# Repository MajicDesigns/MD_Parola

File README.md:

# Library for modular scrolling LED matrix text displays

[Version 1.0 Video](http://www.youtube.com/watch?v=JgzVCSFaz3I)

[Version 2.0 Video](http://www.youtube.com/watch?v=u1iELyROjW8)

[Sprites Animation Video](http://www.youtube.com/watch?v=tfwAHx0MTxU)

[Library Documentation](https://majicdesigns.github.io/MD_Parola/)

Parola is a modular scrolling text display using MAX7219 or MAX7221 LED matrix display controllers using Arduino. The display is made up of any number of identical modules that are plugged together to create a wider/longer display.
* Text left, right or center justification in the display
* Text scrolling, entry and exit effects
* Control display parameters and animation speed
* Support for hardware SPI interface
* Multiple virtual displays (zones) in each string of LED modules
* User defined fonts and/or individual characters substitutions
* Support for double height displays
* Support for mixing text and graphics on the same display

The aim was to create a 'lego-like' LED matrix display, using standard 8x8 LED matrices. The software supports this flexibility through a scalable approach that only requires the definition of the number of modules to adapt existing software to a new configuration.

If you like and use this library please consider making a small donation using [PayPal](https://paypal.me/MajicDesigns/4USD)

The Parola software has a dependency on the [MD_MAX72xx Arduino library](https://github.com/MajicDesigns/MD_MAX72xx) which implements hardware functions of the LED matrix. The library needs to be configured for the type of matrices being used - please refer to the hardware section of documentation for the [MD_MAX72xx library](https://majicdesigns.github.io/MD_MAX72XX/page_hardware.html).

Parola discussion on the [Arduino forum](http://forum.arduino.cc/index.php?topic=171056.0) and kits available from [ElectroDragon](http://www.electrodragon.com/product/dot-matrix-chain-display-kit-max7219-v2).

Additional information also at [my blog](http://arduinoplusplus.wordpress.com), search "Parola A to Z".

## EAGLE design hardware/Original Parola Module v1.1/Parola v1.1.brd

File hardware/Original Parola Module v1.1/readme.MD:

Parola hardware documentation files for custom PCB
- Eagle CAD Schematic and Board layout
- SeeedStudio PCB manufacture Gerber files

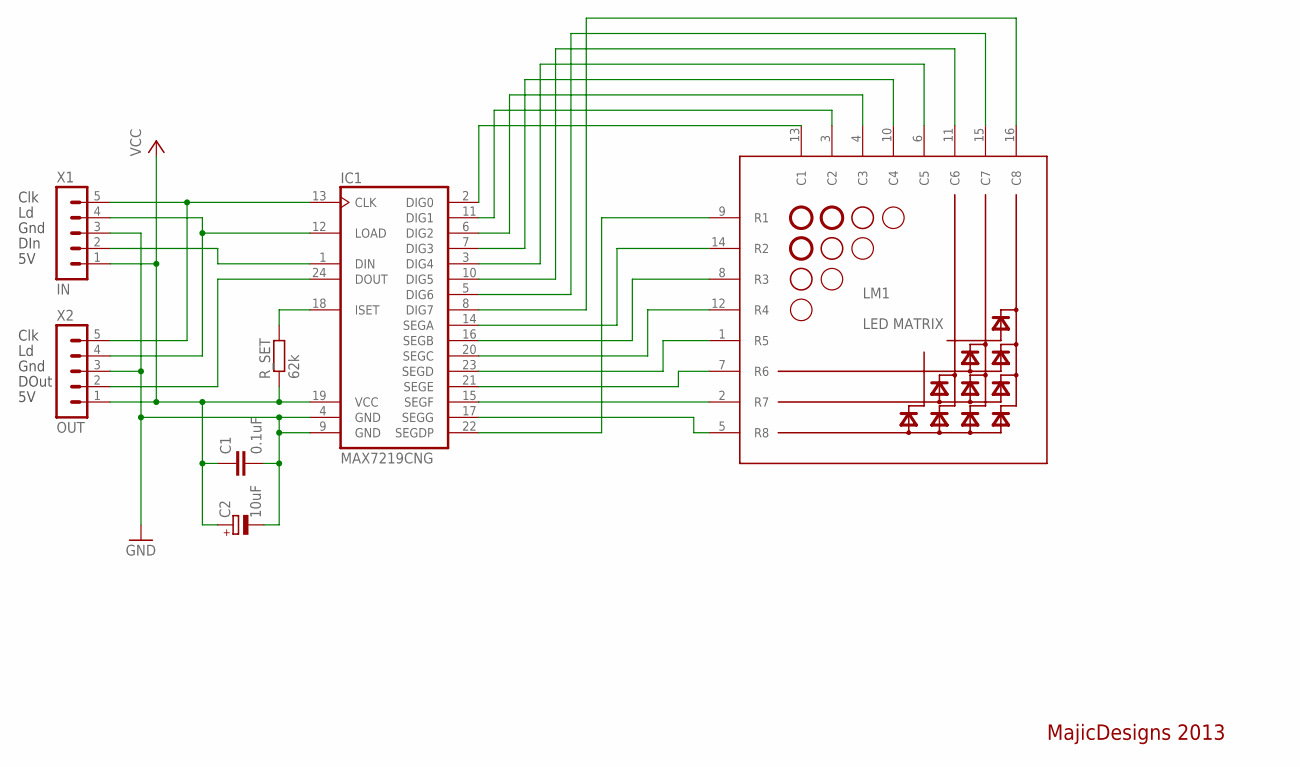
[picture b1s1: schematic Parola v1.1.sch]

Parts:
C1: 0.1uF; C025-024X044
C2: 10uF; E2-5
IC1: MAX7219CNG; DIL24-3
LM1: LED MATRIX; LED_MATRIX
R_SET: 62k; 0207/10
X1: IN; MAR05-1
X2: OUT; MAR05-1

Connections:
GND: C1.2, C2.-, IC1.4 (GND), IC1.9 (GND), X1.3, X2.3
unnamed: IC1.17 (SEGG), LM1.5 (R8)
unnamed: IC1.15 (SEGF), LM1.2 (R7)
unnamed: IC1.21 (SEGE), LM1.7 (R6)
unnamed: IC1.23 (SEGD), LM1.1 (R5)
unnamed: IC1.20 (SEGC), LM1.12 (R4)
unnamed: IC1.16 (SEGB), LM1.8 (R3)
unnamed: IC1.14 (SEGA), LM1.14 (R2)
unnamed: IC1.22 (SEGDP), LM1.9 (R1)
unnamed: IC1.8 (DIG7), LM1.16 (C8)
unnamed: IC1.5 (DIG6), LM1.15 (C7)
unnamed: IC1.10 (DIG5), LM1.11 (C6)
unnamed: IC1.3 (DIG4), LM1.6 (C5)
unnamed: IC1.7 (DIG3), LM1.10 (C4)
unnamed: IC1.6 (DIG2), LM1.4 (C3)
unnamed: IC1.11 (DIG1), LM1.3 (C2)
unnamed: IC1.2 (DIG0), LM1.13 (C1)
unnamed: IC1.13 (CLK), X1.5, X2.5
unnamed: IC1.12 (LOAD), X1.4, X2.4
unnamed: IC1.1 (DIN), X1.2
unnamed: IC1.24 (DOUT), X2.2
unnamed: IC1.18 (ISET), R_SET.2
VCC: C1.1, C2.+, IC1.19 (VCC), R_SET.1, X1.1, X2.1

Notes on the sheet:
Clk
Gnd
DIn
DOut
MajicDesigns 2013

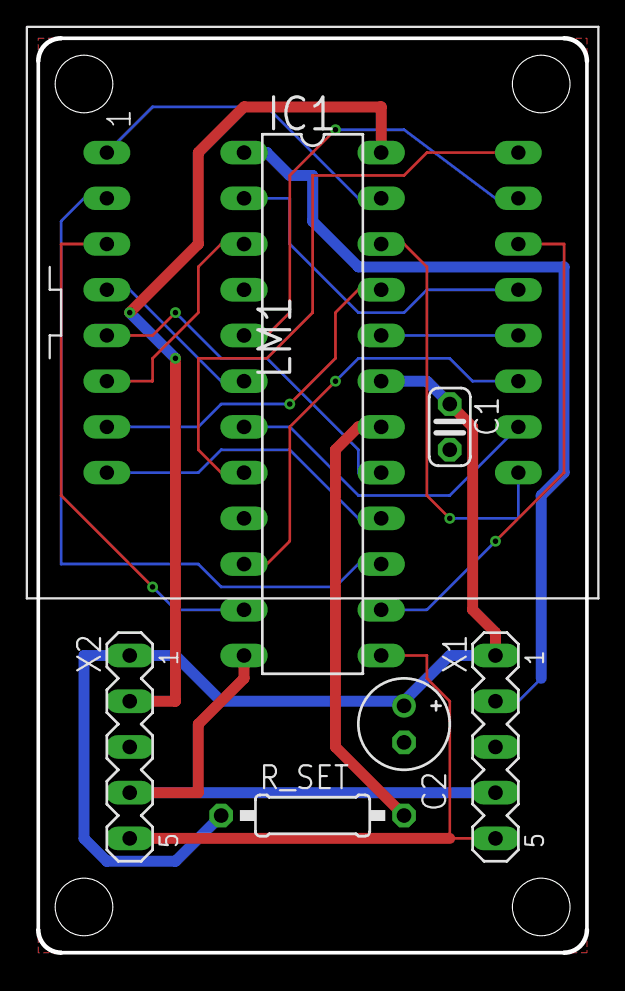
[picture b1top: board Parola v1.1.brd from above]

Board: 2 copper layers, 30.5 x 50.8 mm, 7 parts (0 on the bottom side), 23 nets.

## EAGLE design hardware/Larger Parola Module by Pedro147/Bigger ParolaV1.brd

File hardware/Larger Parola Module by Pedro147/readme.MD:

Bigger Parola V1

For anyone wanting to use slightly larger 60 mm LED matrices, here are the Eagle board and schematic files, seeedstudio gerbers and custom 8 x 8 LED matrix files. Link to Bigger Parola webpage where there are some images of the PCB's and an enclosure containing eight of these display matrices and operating controls. http://www.pedroduino.com/BiggerParolaforArduino.php

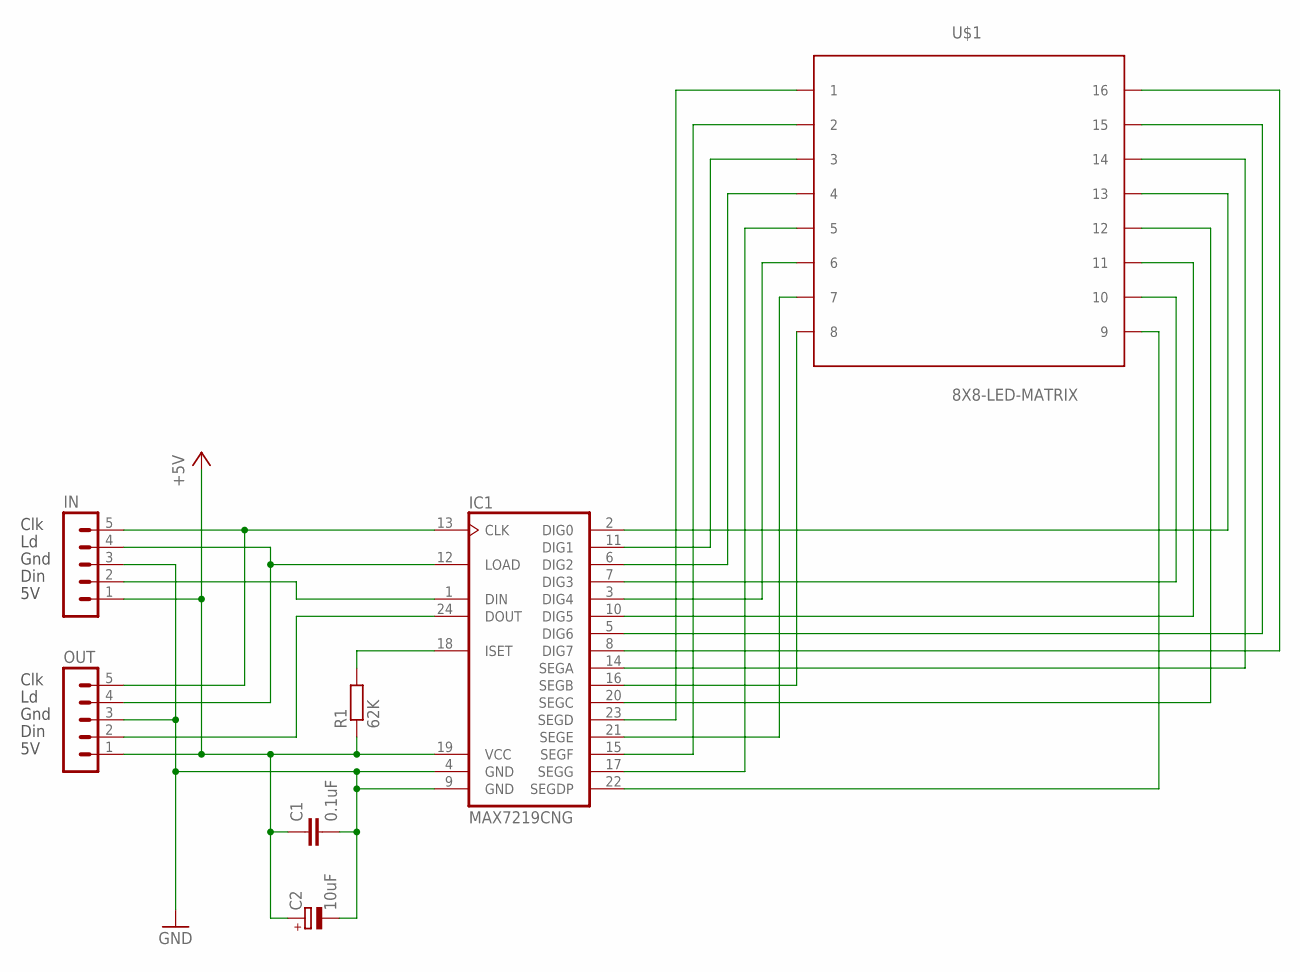
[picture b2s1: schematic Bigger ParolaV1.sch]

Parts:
C1: 0.1uF; C025-024X044
C2: 10uF; E2-5
IC1: MAX7219CNG; DIL24-3
IN: MAR05-1
OUT: MAR05-1
R1: 62K; 0207/10
U$1: 8X8-LED-MATRIX

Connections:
+5V: C1.1, C2.+, IC1.19 (VCC), IN.1, OUT.1, R1.1
GND: C1.2, C2.-, IC1.4 (GND), IC1.9 (GND), IN.3, OUT.3
unnamed: IC1.18 (ISET), R1.2
unnamed: IC1.24 (DOUT), OUT.2
unnamed: IC1.12 (LOAD), IN.4, OUT.4
unnamed: IC1.13 (CLK), IN.5, OUT.5
unnamed: IC1.1 (DIN), IN.2
unnamed: IC1.2 (DIG0), U$1.P$13 (13)
unnamed: IC1.11 (DIG1), U$1.P$3 (3)
unnamed: IC1.6 (DIG2), U$1.P$4 (4)
unnamed: IC1.7 (DIG3), U$1.P$10 (10)
unnamed: IC1.3 (DIG4), U$1.P$6 (6)
unnamed: IC1.10 (DIG5), U$1.P$11 (11)
unnamed: IC1.5 (DIG6), U$1.P$15 (15)
unnamed: IC1.8 (DIG7), U$1.P$16 (16)
unnamed: IC1.14 (SEGA), U$1.P$14 (14)
unnamed: IC1.16 (SEGB), U$1.P$8 (8)
unnamed: IC1.20 (SEGC), U$1.P$12 (12)
unnamed: IC1.23 (SEGD), U$1.P$1 (1)
unnamed: IC1.21 (SEGE), U$1.P$7 (7)
unnamed: IC1.15 (SEGF), U$1.P$2 (2)
unnamed: IC1.17 (SEGG), U$1.P$5 (5)
unnamed: IC1.22 (SEGDP), U$1.P$9 (9)

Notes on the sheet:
Clk
Gnd
Din

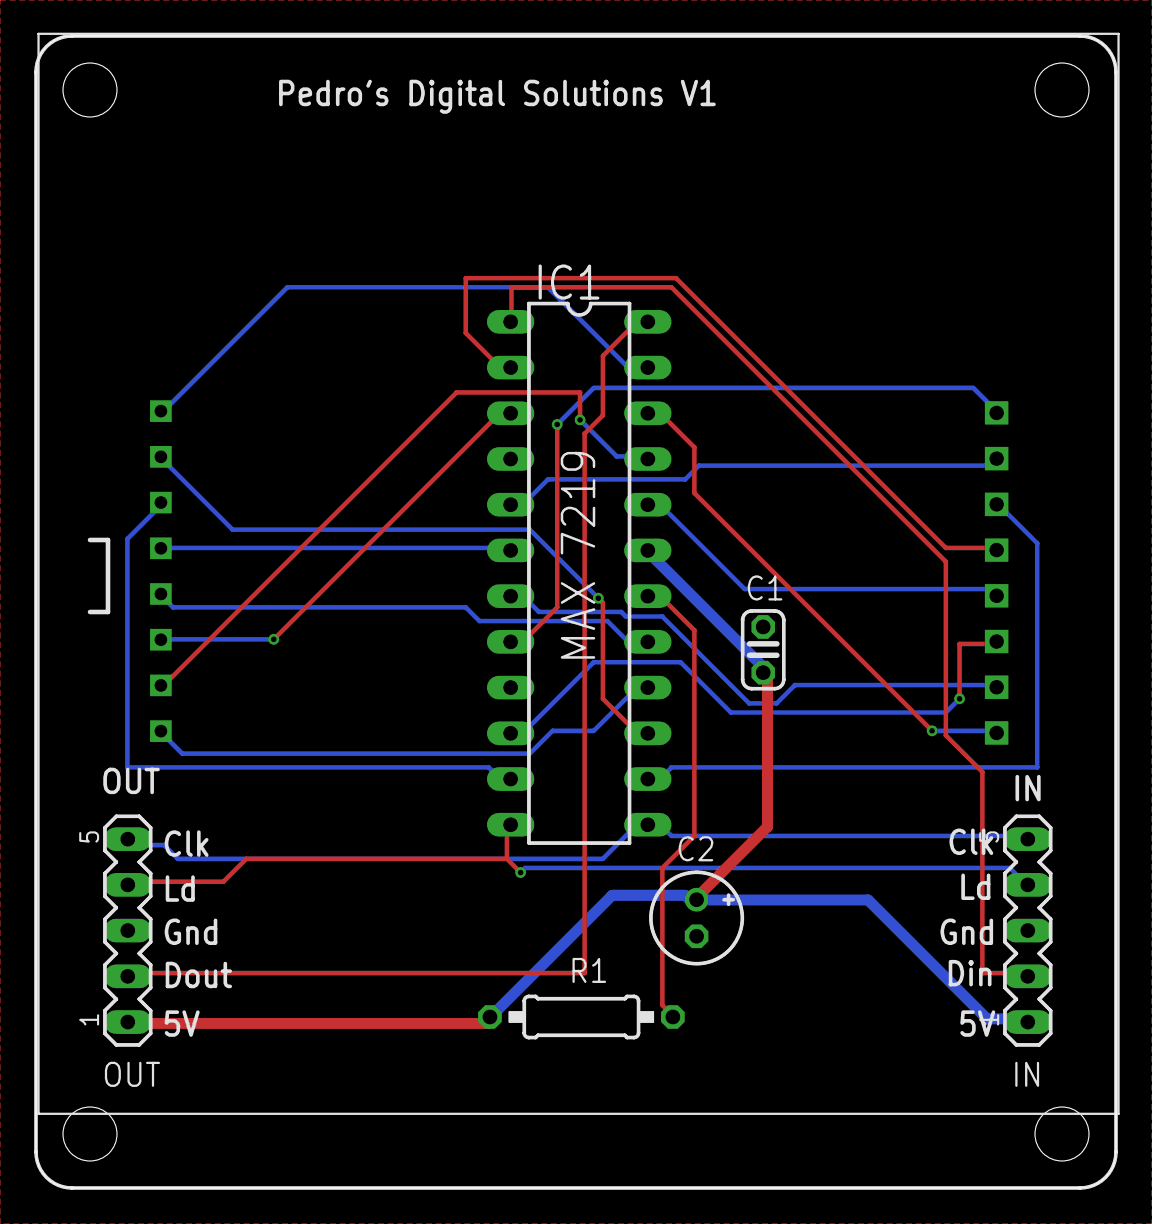
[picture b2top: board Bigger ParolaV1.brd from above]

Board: 2 copper layers, 60.0 x 64.0 mm, 7 parts (0 on the bottom side), 23 nets.

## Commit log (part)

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2013-11-23 First commit on version 1.0
2013-11-24 Changed web addresses to new location; spelling check of header file
2013-12-31 Minor changes
2014-02-15 Reworkd to allow user defined font files.
2014-02-15 Added functionality for usert defined character substitution
2014-02-16 Added animations SCAN_HORIZ, SCAN_VERT, GROW_UP, GROW_DOWN
2014-02-16 Removed static variables from effects functions in preparation for zoning code
2014-02-22 Reworked Parola test example program Fixed number of issues with the display of inverted messages on some effects.
2014-02-22 Adjusted fonts example for Arabic "Arduino" and modern font Test program changed after completion of test shield arrangement
2014-02-25 Added diagonal scrolling animations effects Modified examples to suit Changted H and V scrolling function parameters to be in line with rest
2014-03-09 Snapshot after major changes to MD_MAX library. Appears to still work ok :-) First checkin of images.
2014-03-11 First pass at zoning. Zones implemented in Parola object ready for creation of zone object as stage 2
2014-03-22 Fixed Slice animation with single default zone implementation Useing MD_KeySwitch object in example software
2014-03-22 End of day work for new zones. Still issues with Fonts and definitions but overall working reasonably
2014-03-24 Multi zone implementation completed. Fixed bug with Slice animation Added Zone examples.
2014-03-26 Completed implementation of zoned displays and tested. New examples included.
2014-03-28 Clean up ready for v2.0 release
2014-04-27 Minor corrections to comments and code
2014-07-25 Fixed animation timer bug and changed time profiling debug code
2014-09-06 Fixed animation issues with SCAN_VERT and SLICE. Added Animations Catalog example program. Renamed Doxyfile config file.
2014-09-14 Fixed compile errors woith PROGMEM and IDE v1.5.7
2015-01-31 Version 2.1 Release - includes all changes since version 2.0
2015-02-13 Added Scrolling_ML example
2015-03-03 Added Zone_Mesg example
2015-03-06 Added overloaded displayClear() for zone
2015-03-07 Fixed bug in SLICE effect when text was too long for display
2015-03-31 src folder added for Library Manager (IDE 1.6.2)
2015-03-31 Version 2.2 code base
2015-06-15 Changes to accomodate adjustments to the MD_KeySwitch library
2015-07-19 - Added set/getScrollSpacing() methods - Added associated Scrolling_Spacing example New method allows for scrolled text to be on the display before the previous text has left the display.
2015-07-19 - Added set/getZoneEffect with FLIP_LR and FLIP_UD - Added associated Zone_Mirror example - Fixed minor bugs and documentation
2015-07-20 Minor tidy up from last commit - keywords.txt missing get/setZoneEffect() - Added flip test ui switch to Parola_Test - Changed timing in test catalog after fixing variable reference bug.
2015-08-17 Added MESH animation Souce code set for version 2.3 release
2015-09-05 Minor changes due to MD_DS1307 library change
2015-09-19 Added example to demonstrate dynamic zones
2015-09-24 Added synchZoneStart() method for zonbe animation
2015-09-27 Added double height example code by Arek00 Modifed all examples to conditionally include <SPI.h>
2015-10-03 Added additional example file that uses double height foints created with MD_MAX72xx font builder.
2015-10-20 Added HelloWorld example
2016-01-02 Added FADE effect. Reviewed and reorganised some documentation.
2016-01-02 Added #defines ENA_* for granular selection of animations (memory saving) Release v2.4 code base
2016-08-31 Added Parola_Ambulance example to show reversed text
2016-11-14 - Added in doc files - Added README.md - Changed branding to MD_ diamond
2016-11-14 - README.md edit
2016-11-14 Edited comments
2016-11-16 - Edited deprecated USE_LIBRARY_SPI from examples - Rearranged documentation folder for Github pages
2016-11-16 ignore
2016-11-16 ignore again
2016-11-16 Added link to github pages site
2016-11-20 - Changed enumerated with prefix PA_ to prevent clashes. This will break existing code but easy edit fix. - Updated documentation files
2016-11-23 Repositories renamed
2016-12-05 Trasnferred hardware files from codeplex site
2016-12-12 - Edited main library core rouines to allow scrolling in double height mode - Eliminated trailing char separator from displayed string - Adjusted some animations to allow for changes to core utility 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
2016-12-12 Removed debug output from examples
2016-12-23 Fixed up all Font based examples
2016-12-24 - Added Print class extensions for .print functionality - Added Print example - Updated documentation
2016-12-30 Added ESP8266 example Cleaned up keywords.txt, compiler warnings
2016-12-30 Fixed ESP8266 comment typos
2017-01-01 Doc update
2017-01-03 - Added pointer to documentation - Cleaned up looping logic in Double_Height examples
2017-01-12 Fixed PA_SCROLL_RIGHT bug when in double height mode
2017-01-12 Updated homepage url
2017-01-16 Added displayShutdown() method, updated doc and Parola_Test example
2017-01-19 Included Gerber files
2017-01-21 Corrected alignment offset problems in low level functions
2017-01-29 Change libray.properties for consistency
2017-02-05 Full review of double height functionality, mods as required Added Double_Height_Test example Cleaned up some example files
2017-02-12 Added Parola_UFT-8_Display example for double multi-byte character handling
2017-03-07 - Reworked Scrolling examples to not need array index for buffering - Fixed browser incompatibiity for ESP8266 example
2017-03-10 Adjusted print() to take library current parameters rather than forced to CENTER.
2017-04-09 Changed Scrolling example to parametrize more options Fixed bug: single blank column using SCROLL_LEFT with PA_LEFT alignment
2017-04-10 Added .gitattribute file to control auto detection of language on githib.com
2017-04-11 Added RANDOM text effect
2017-04-13 Fixed RANDOM effect locking issue
2017-05-05 Added Bluetooth Control example
2017-05-06 AI2 App adjustment
2017-05-30 Added double height Russian example
2017-05-31 Added Scrolling_Menu example
2017-06-02 Updated Scroll_Menu examples with changes to menu library
2017-07-09 Added vertical scrolling example
2017-08-20 SCAN effect split into 2 variants - append 0 for scanning a blank colum through text, append 1 for scanning the text column on blank field (previous behaviour).
2017-08-20 Examples updated
2017-08-27 Fixed reversing issues with new SCAN effect. Renamed enum to VERTX, HORIZX.
2017-09-14 Corrected examples with incorrect SCAN codes
2017-10-22 Fixed bug with GROW, SCAN and WIPE emerged when using one module only.
2017-10-28 Removed hard coded buffer size for font character buffer
2017-10-28 Corrected buffer size for inter char spacing
2017-11-18 Changed MD_KeySwitch to new MD_UISwitch library
2017-12-09 MAX_ZONES workaround for errors when dynamic allocation is used for _Z variable. Cleaned up most compiler warnings.
2017-12-23 README.md: fix link to MAX72xx github
2017-12-24 Adjusted Scrolling_Menu example for changes to MD_Menu library
2018-01-03 Adjusted Scrolling_Menu example for new INT menu definitions
2018-03-26 Added support for mixing text & graphics, plus example demonstraing use.
2018-03-26 Renamed to TG and amended comments as T+G not valid filename for IDE
2018-04-13 Fixed bug with last text column persisting for SCAN_HORIZ and SCAN_HORIZX effect.
2018-04-13 Added sprite based text effects
2018-04-18 Reworked sprite effects to enable user sprites as more sustainable in long run. Added Sprites example.
2018-04-19 Reworked sprite effects to enable user sprites as more sustainable in long run. Removed all internal sprite effects. Added Sprites example.
2018-04-19 Update after merged masters
2018-04-19 Fixed bug with ESP8266 compile
2018-04-22 Minor corrections to previous version examples and keyword.txt. Added help text on sprite animations.
2018-04-25 Rearranged Sprites example and minor doc updates.
2018-06-09 Changes due to changes in MD_MAX72xx
2018-07-08 Added getFont functions
2018-07-10 Cleanup up double height examples based on previous #defines
2018-07-10 Added getFont() method
2018-08-03 Fixed another compile error with ESP8266.
2018-12-06 Description of how to rotate display 180°
2018-12-23 Stopped inter char spacing with zero length character
2018-12-24 Fixed issues caused by inter char spacing fix in v3.0.2
2019-03-31 Remove wrong typedef
2019-03-31 Reorder initializers to match declaration order
2019-03-31 Remove trailing whitespaces
2019-03-31 Replace tabs by spaces
2019-03-31 Remove superfluous empty lines
2019-03-31 Add spaces around operators
2019-03-31 Use const char* parameter instead of char* parameter
2019-05-13 Allow predefining MD_Parola macros when invoking C++ compiler
2019-05-27 Initialize _suspend and _lastRunTime in MD_PZone constructor
2019-05-30 Minor fixes
2019-05-30 Unitialized variables fixed
2019-07-29 LIbrary.properties changed
2019-07-31 Changed to use 16 bit character code Checked all examples for clean compile with current version
2019-10-14 Reverted back to dynamically allocated zones removed in v2.6.6. Tested 22 zones, seems ok.
2019-10-14 VS add build file to ignore in new version
2019-12-30 Correct dependency name
    Previously, the library.properties depends field was defined as MD_MAX72xx, but the library name is MD_MAX72XX and the Arduino Library Manager dependencies system is case sensitive.
2020-02-19 FONTDATA.H
    test
2020-08-15 Updated help files
2020-08-16 setSpeed() allows setting IN and OUT speed independently.
2020-08-17 Added Animation_2Speed example Workaround for issue #56 included in library
2020-08-18 Fixed setIntensity()
2020-08-19 3.5.1 release
2020-08-21 3.5.2
    - Added displayAnimationTerminate to terminate an animation
    - Renamed setSpeed(uint16_t speedIn, uint16_t speedOut) in setSpeedInOut
2020-08-21 3.5.2
    fixed typos in the comments
2020-08-21 Fixed ambiguous overloading setSpeed(uint8_t zone, uint16_t spd) and setSpeed(uint16_t spdIn, uint16_t spdOut)
2020-10-04 Fixed behaviour of SCROLL_UP, DOWN, UP_LEFT, UP_RIGHT, DOWN_LEFT, DOWN_RIGHT for inverted display
2020-10-07 Fixed Error in Parola_Helloworld example
    Line 35 - Changed PA_SCRO__DOWN to PA_SCROLL_DOWN
2020-10-07 Release for fixed typo in HelloWorld example
2020-12-22 Fixed erratic zone scrolling behavior in introduced with changes to 3.5.3 Added README.md to examples folder
2020-12-29 Added TG_Combo, TG_Coord and TG_Zones examples. Deleted Test_TG example.
2021-03-09 Fixed ENA_* no longer working (compiler changes)
2021-05-29 Fixed issues with text occasionally remaining on edge of display for diagonal scroll effects
2021-05-29 Slight mods to Test example.
2022-01-29 Changed user characters data to be constant
2022-01-29 Fix spacing
2022-05-11 Added constructor with specified SPI interface
2022-05-11 Minor edit to examples readme
2022-05-11 Fixed misspelled parameter
2022-11-16 Fixed uninitialised _intensity class variable.
2023-06-02 begin() returns bool status fixed intensity initialisation of multi-zone displays at startup
2023-07-03 added getIntensity() to Parola object
2024-01-27 Removed debug message remnants from begin()
2024-04-03 Changed uint8_t to uint16_t animation loop indices; added contributed speites
2025-10-31 Fixed library.properties case issue
2025-10-31 Reversed incorrect changes
2025-10-31 Fixed wrong changes
2025-11-21 Fixed issues with Parola_Diag code (PA_SCROLL_UP/DOWN_LEFT/RIGHT) behavior with zones
